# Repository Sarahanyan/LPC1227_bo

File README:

This is small breakuot board for LPC1227 a similar, to allow breadboarding with smaller footprint than nice, but huge LPCXpresso boards.
Design files are for Eagle 6.
Attached is also test code to excercise LED on PIO1_6

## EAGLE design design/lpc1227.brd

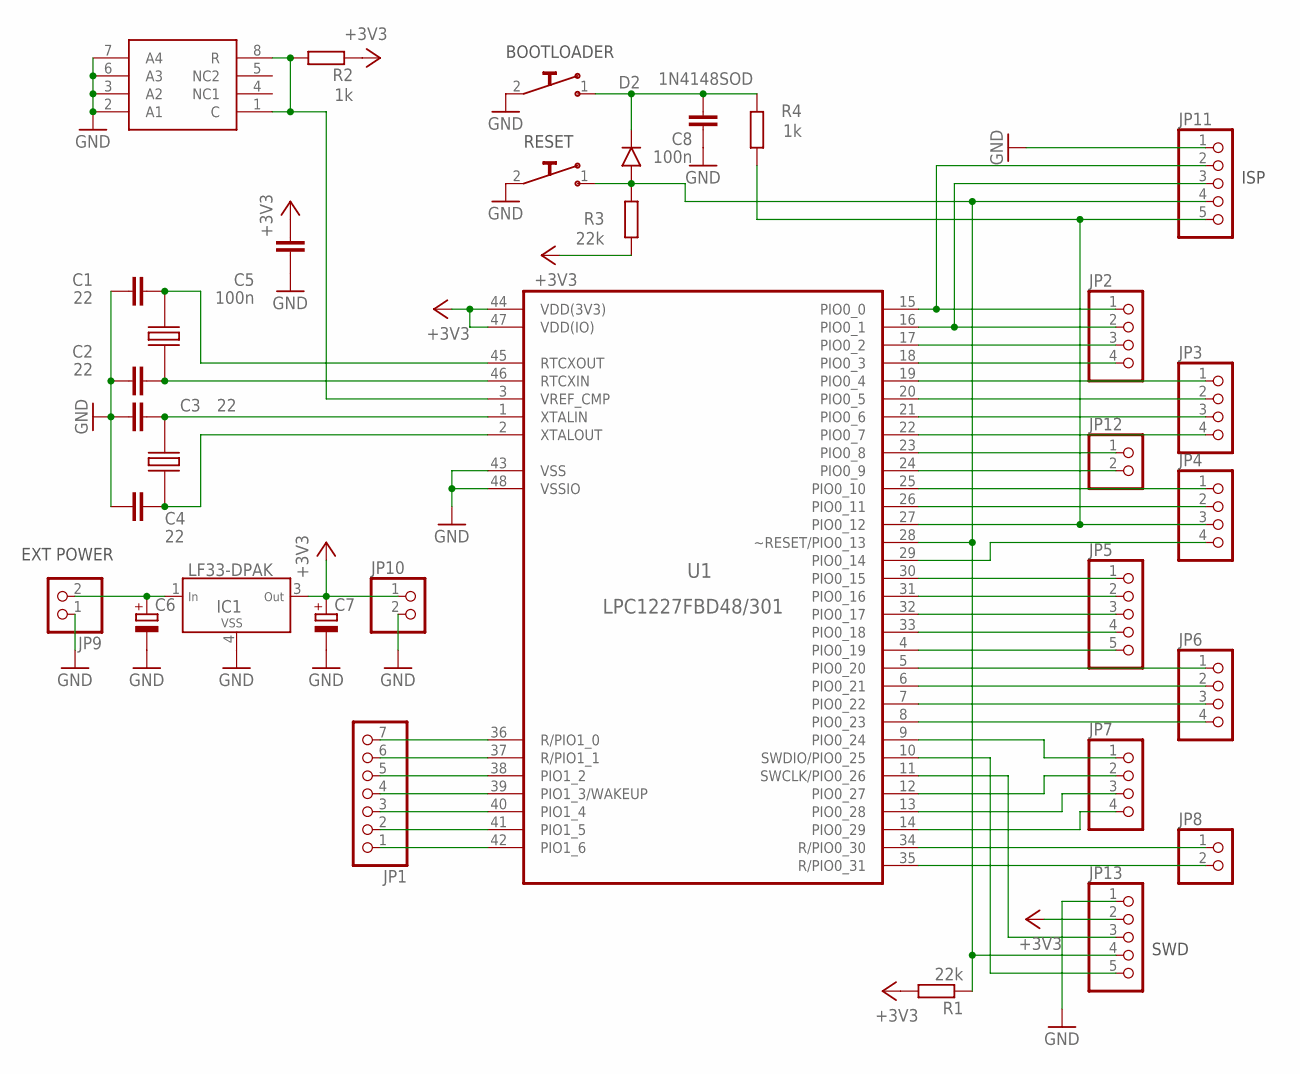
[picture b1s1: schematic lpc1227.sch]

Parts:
C1, C2, C3, C4: 22; R0805
C5, C8: 100n; R0805
C6, C7: CPOL-EUSMCA; SMC_A
D2: 1N4148SOD; SOD-80
IC1: LF33-DPAK; DPAK
JP1: PINHD-1X07_2.54-S; 1X07-S
JP2, JP3, JP4, JP6, JP7: PINHD-1X04_2.54-S; 1X04-S
JP5, JP11, JP13: PINHD-1X05_2.54-S; 1X05-S
JP8, JP9, JP10, JP12: PINHD-1X02_2.54-S; 1X02-S
K1, K2: SWITCH_MINI; SW_SMD_MINI
R1, R3: 22k; R0805
R2, R4: 1k; R0805
U1: LPC1227FBD48/301; QFP50P900X900X160-48N
U$2: TL431_SO8; SO8
X1: 12M; TC38
X2: 32k; TC38

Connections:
+3V3: C5.2, C7.+, IC1.3 (OUT), JP10.1, JP13.2, R1.2, R2.1, R3.1, U1.44 (VDD(3V3)), U1.47 (VDD(IO))
GND: C1.1, C2.1, C3.1, C4.1, C5.1, C6.-, C7.-, C8.1, IC1.4 (VSS), JP9.1, JP10.2, JP11.1, JP13.1, K1.2, K2.2, U1.43 (VSS), U1.48 (VSSIO), U$2.2 (A1), U$2.3 (A2), U$2.6 (A3), U$2.7 (A4)
unnamed: JP13.5, U1.10 (SWDIO/PIO0_25)
unnamed: JP13.3, U1.11 (SWCLK/PIO0_26)
unnamed: C3.2, U1.1 (XTALIN), X2.P$2
unnamed: C4.2, U1.2 (XTALOUT), X2.P$1
unnamed: C1.2, U1.45 (RTCXOUT), X1.P$2
unnamed: C2.2, U1.46 (RTCXIN), X1.P$1
unnamed: R2.2, U1.3 (VREF_CMP), U$2.1 (C), U$2.8 (R)
unnamed: JP4.4, U1.29 (PIO0_14)
unnamed: JP1.1, U1.42 (PIO1_6)
unnamed: JP1.2, U1.41 (PIO1_5)
unnamed: JP1.3, U1.40 (PIO1_4)
unnamed: JP1.4, U1.39 (PIO1_3/WAKEUP)
unnamed: JP1.5, U1.38 (PIO1_2)
unnamed: JP1.6, U1.37 (R/PIO1_1)
unnamed: JP1.7, U1.36 (R/PIO1_0)
unnamed: JP2.1, JP11.2, U1.15 (PIO0_0)
unnamed: JP2.2, JP11.3, U1.16 (PIO0_1)
unnamed: JP2.3, U1.17 (PIO0_2)
unnamed: JP2.4, U1.18 (PIO0_3)
unnamed: JP3.1, U1.19 (PIO0_4)
unnamed: JP3.2, U1.20 (PIO0_5)
unnamed: JP3.3, U1.21 (PIO0_6)
unnamed: JP3.4, U1.22 (PIO0_7)
unnamed: JP4.1, U1.25 (PIO0_10)
unnamed: JP4.2, U1.26 (PIO0_11)
unnamed: JP4.3, JP11.5, R4.1, U1.27 (PIO0_12)
unnamed: JP5.1, U1.30 (PIO0_15)
unnamed: JP5.2, U1.31 (PIO0_16)
unnamed: JP5.3, U1.32 (PIO0_17)
unnamed: JP5.4, U1.33 (PIO0_18)
unnamed: JP6.1, U1.5 (PIO0_20)
unnamed: JP6.2, U1.6 (PIO0_21)
unnamed: JP6.3, U1.7 (PIO0_22)
unnamed: JP6.4, U1.8 (PIO0_23)
unnamed: JP7.4, U1.14 (PIO0_29)
unnamed: JP7.3, U1.13 (PIO0_28)
unnamed: JP7.2, U1.12 (PIO0_27)
unnamed: JP7.1, U1.9 (PIO0_24)
unnamed: JP8.1, U1.34 (R/PIO0_30)
unnamed: JP8.2, U1.35 (R/PIO0_31)
unnamed: C6.+, IC1.1 (IN), JP9.2
unnamed: JP12.1, U1.23 (PIO0_8)
unnamed: JP12.2, U1.24 (PIO0_9)
unnamed: JP5.5, U1.4 (PIO0_19)
unnamed: D2.A, JP11.4, JP13.4, K1.1, R1.1, R3.2, U1.28 (~RESET/PIO0_13)
unnamed: C8.2, D2.K, K2.1, R4.2

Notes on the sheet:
BOOTLOADER
RESET
SWD
ISP
EXT POWER

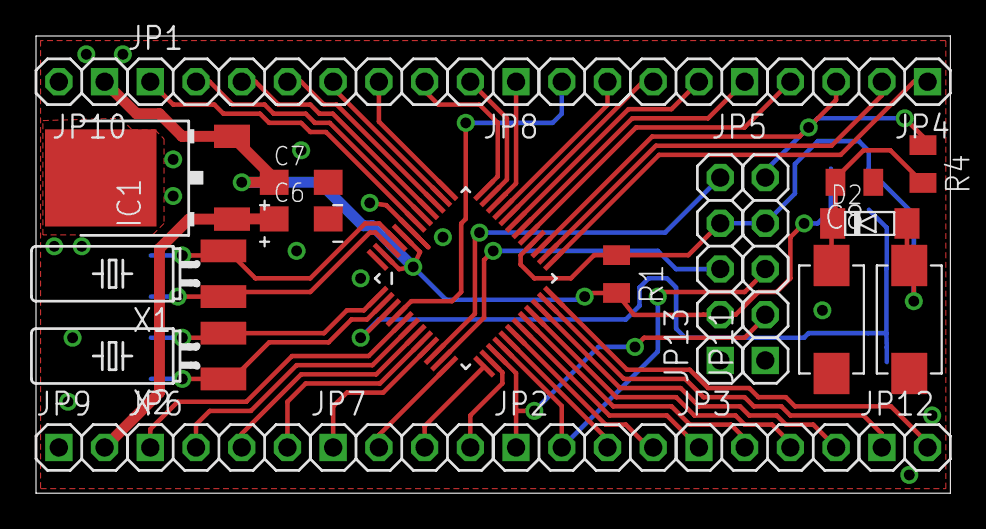
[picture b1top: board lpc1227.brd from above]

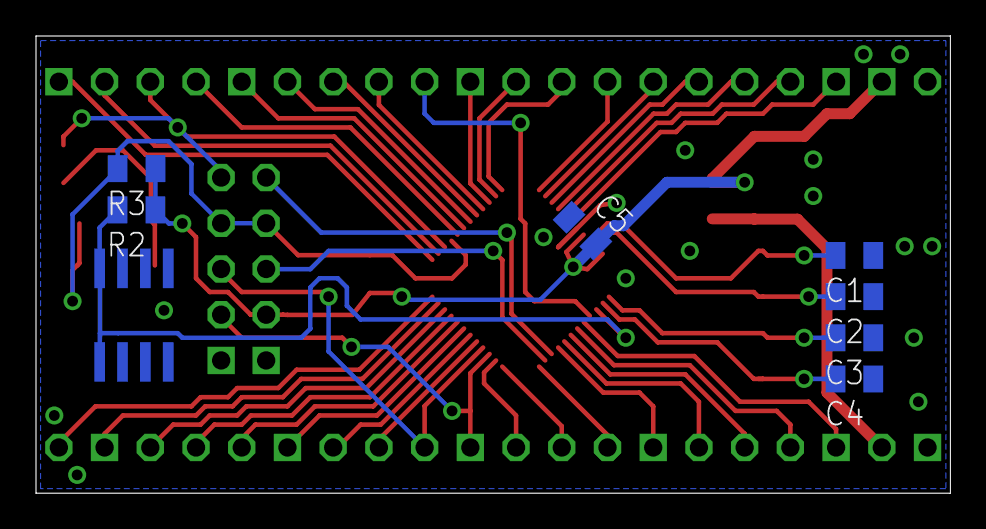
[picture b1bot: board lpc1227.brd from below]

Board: 2 copper layers, 50.8 x 25.4 mm, 33 parts (8 on the bottom side), 48 nets.

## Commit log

2014-03-18 ver 1
    inital release
2014-03-19 src_ver1
2014-03-19 dec 1
2014-03-19 schem 1
2014-03-19 r ver 2
